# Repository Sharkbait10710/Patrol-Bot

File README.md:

# Patrol-Bot
Objective:
Reduce the need of security cameras and utilize a patrolling robot that provides real-time video footage as it patrols around a person's house.

Capability: 
When battery is low, patrol bot will find a power outlet and self-charge.
Can map out house / room layout
Take remote commands to check different locations throughout a house

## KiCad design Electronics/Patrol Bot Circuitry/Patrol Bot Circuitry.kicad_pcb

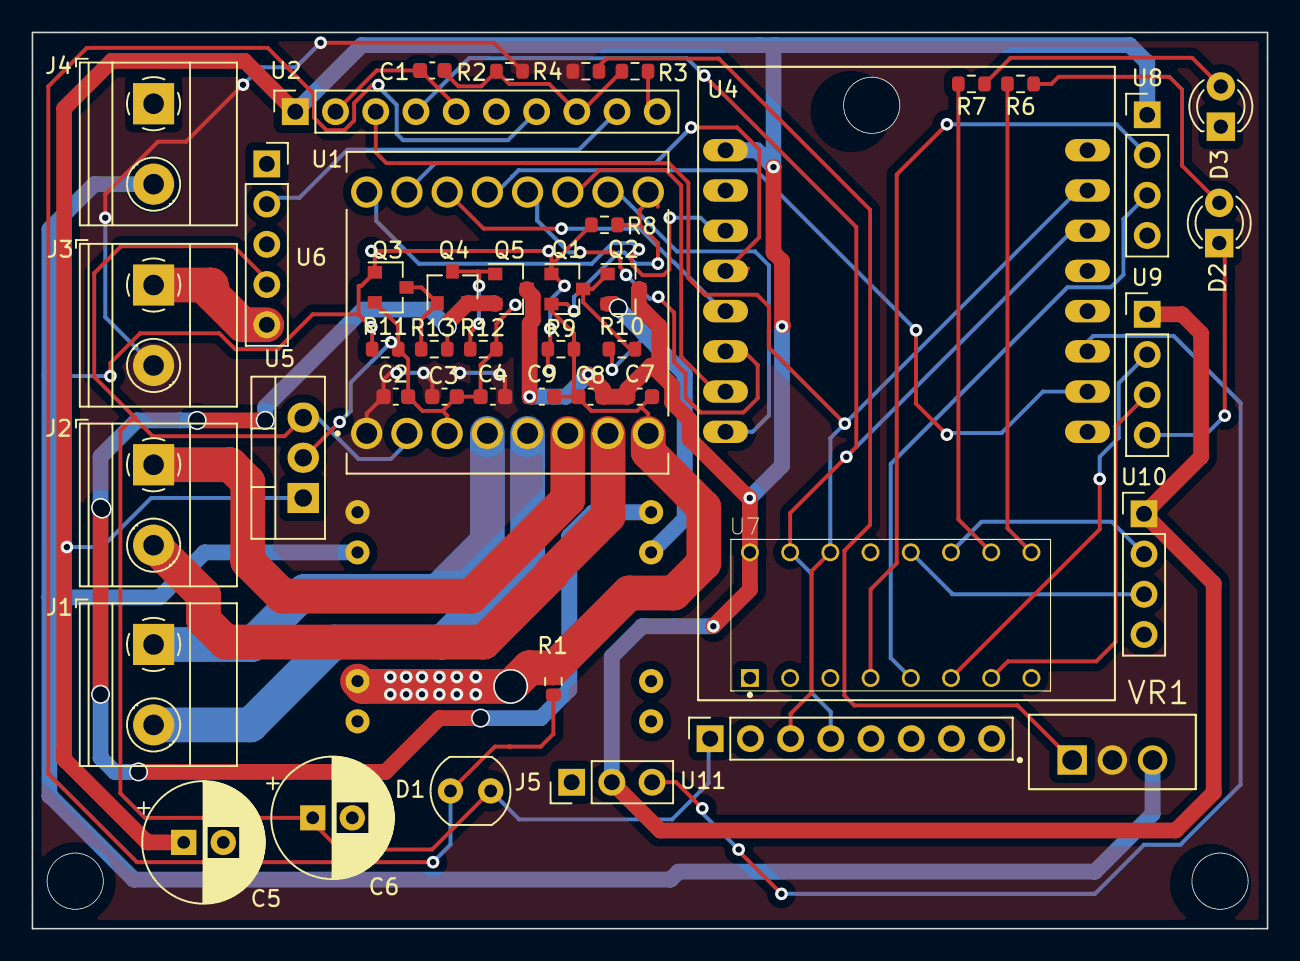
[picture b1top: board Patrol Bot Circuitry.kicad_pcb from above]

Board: 2 copper layers, 78.0 x 56.6 mm, 46 parts (1 on the bottom side), 38 nets.

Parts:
C1, C4, C7: 0.47u; C_0603_1608Metric
C2: 0.01n; C_0603_1608Metric
C3, C8: 0.1u; C_0603_1608Metric
C5, C6: 470u; CP_Radial_D7.5mm_P2.50mm
C9: 0.01u; C_0603_1608Metric
D1: D_Photo; R_LDR_4.9x4.2mm_P2.54mm_Vertical
D2, D3: LED; LED_D3.0mm
J1: Left_Motor; TerminalBlock_Phoenix_MKDS-1,5-2-5.08_1x02_P5.08mm_Horizont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
J2: Right_Motor; TerminalBlock_Phoenix_MKDS-1,5-2-5.08_1x02_P5.08mm_Horizont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
J3: Battery; TerminalBlock_Phoenix_MKDS-1,5-2-5.08_1x02_P5.08mm_Horizont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
J4: AC_DC_10V; TerminalBlock_Phoenix_MKDS-1,5-2-5.08_1x02_P5.08mm_Horizont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
J5: Servo Motor; PinHeader_1x03_P2.54mm_Vertical
Q1, Q3: Q_NMOS_GSD; SOT-23
Q2, Q4, Q5: Q_PMOS_GSD; SOT-23
R1, R3: 200K; R_0603_1608Metric
R2: 620K; R_0603_1608Metric
R4: 2K; R_0603_1608Metric
R6, R7: 300; R_0603_1608Metric
R8, R9, R10, R11, R12, R13: 200k; R_0603_1608Metric
U1: ROB-14450; MODULE_ROB-14450
U2: ADS1115; PinSocket_1x10_P2.54mm_Vertical
U3: MP1584EN
U4: ESP32-CAM
U5: LM2931-3.3_TO220; TO-220-3_Vertical
U6: MAX9814; PinSocket_1x05_P2.54mm_Vertical
U7: PCF8574; DIP794W45P254L1969H508Q16
U8, U9, U10: HC-SR04; PinHeader_1x04_P2.54mm_Vertical
U11: MPU-6050; PinSocket_1x08_P2.54mm_Vertical
VR1: LM317T_NOPB; TO254P1054X470X1955-3

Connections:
+5V: C5.1, C7.1, C8.1, C9.1, J5.2, Q2.3, Q5.3, U2.1, U4.P$1, U5.1, U7.16, U8.1, U9.1, U10.1
+10V: J4.2, Q1.1, Q3.1, R8.1, R9.1, R11.1, U3.7, VR1.3
/3.3V: C6.1, D1.2, U1.2, U5.3, U6.4, U11.1
/A1: C1.2, R2.2, R3.1, U2.8
/A2: U2.9, U6.2
/Battery: C2.2, C3.2, C4.2, J3.2, R2.1, R4.1, U1.1, U3.8, VR1.2
/IO1: U1.13, U4.P$10
/IO3: J5.3, U4.P$11
/SCL: U2.3, U4.P$15, U7.14, U11.3
/SDA: U2.4, U4.P$14, U7.15, U11.4
GND: C1.1, C2.1, C3.1, C4.1, C5.2, C6.2, C7.2, C8.2, C9.2, D2.1, D3.1, J3.1, J4.1, J5.1, Q1.2, Q3.2, R1.2, R3.2, R8.2, R9.2, R11.2, R12.2, U1.3, U1.8, U1.9, U2.2, U2.5, U2.10, U3.3, U3.4, U3.5, U3.6, U4.P$9, U5.2, U6.5, U7.1, U7.2, U7.3, U7.8, U8.4, U9.4, U10.4, U11.2, U11.7
unnamed: D1.1, R1.1, U2.7
unnamed: D2.2, R6.1
unnamed: D3.2, R7.1
unnamed: J1.1, U1.4
unnamed: J1.2, U1.5
unnamed: J2.1, U1.6
unnamed: J2.2, U1.7
unnamed: Q1.3, Q2.1, R10.2
unnamed: Q2.2, R10.1, U3.2
unnamed: Q3.3, Q4.1, R13.2
unnamed: Q4.2, Q5.2, R13.1, U3.1
unnamed: Q4.3, Q5.1, R12.1
unnamed: R4.2, VR1.1
unnamed: R6.2, U7.9
unnamed: R7.2, U7.10
unnamed: U1.10, U4.P$8
unnamed: U1.11, U4.P$7
unnamed: U1.12, U4.P$6
unnamed: U1.14, U4.P$5
unnamed: U1.15, U4.P$4
unnamed: U1.16, U4.P$3
unnamed: U7.4, U8.2
unnamed: U7.5, U8.3
unnamed: U7.6, U9.2
unnamed: U7.7, U9.3
unnamed: U7.11, U10.2
unnamed: U7.12, U10.3

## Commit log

2021-11-18 Updated Materials
2021-11-20 Started KiCAD Schematic
    Altium is annoying, so I'm using KiCAD
2021-11-26 A lot
2021-12-07 Circuit Update
2021-12-14 Reorganized schematic to aid debugging.
2021-12-15 Finished debugging schematic
2021-12-17 Finish PCB Board
    Still needs evaluation
2021-12-23 CAD Upload 1
2021-12-23 CAD Upload 2
2021-12-23 CAD Upload 3
2021-12-24 CAD Upload 4
2021-12-25 Software Upload 1
2021-12-25 Sofware Upload 2
2021-12-26 Software Uplode 3
2021-12-26 Software Upload 4
2021-12-28 Software Update 5
2021-12-28 Validation 1
2021-12-29 Fixed Power Management Switches
2022-01-02 Redesigned PCB / Mechanical Drawing
    ESP32-cam not connecting to Wifi -> must DEBUG
2022-01-04 GUI is All Setup for Data and Camera Acquisition
    Ready to purchase remaining components
2022-01-06 Software Upload 6
2022-01-07 Software Upload 7
2022-01-07 Corrected Software Mistakes 1
2022-01-10 Added XY Plot
2022-04-07 Save
